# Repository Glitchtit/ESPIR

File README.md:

# ESPIR — Zigbee IR Blaster for Home Assistant

A Home Assistant–controlled IR blaster built on the **ESP32-C6**, connected over
**Zigbee** to a **Zigbee2MQTT (Z2M)** coordinator. It **learns** IR codes from your
existing physical remotes and **replays** them on command, so HA buttons map 1:1 to
"press button → appliance fires the learned signal."

## Topology

```
[remote] --IR--> [VS1838B] --RMT RX--> MASTER (DevKitC-1, USB, Zigbee Router)
                                          |  NVS slots, custom ZCL cluster 0xFC00
                                          |  +--RMT TX--> [SZHJW] --IR--> appliance
                                          v
                       Zigbee <--> Z2M (z2m/espir.js) <--> Home Assistant
                                          |                       |
                              learn / send / read code     buttons + scripts
                                          v
        replication (HA script): copy master's learned code -> each SLAVE
                                          v
                       SLAVE (XIAO C6, LiPo, Sleepy End Device) --IR--> local appliance
```

- **Master** (ESP32-C6-DevKitC-1, USB-powered Zigbee **Router**): **learns** by raw-capturing
  from a **VS1838B** receiver and **transmits** through an **SZHJW** dual-LED module — both on
  the RMT peripheral; stores codes in NVS. Always-on, so it responds instantly and extends the
  Zigbee mesh.
- **Slave** (Seeed XIAO ESP32-C6, LiPo **Sleepy End Device**): transmit-only repeater for
  coverage in another spot, using the SZHJW dual-LED emitter (RMT). Receives learned codes
  from the master via a replication path.

> **Protocol note:** raw capture learns essentially **any** remote; NEC is auto-compacted to
> `{address, command}` for cheap storage/replication. Master and slaves share the RMT backend,
> so codes are fully interoperable.

## Why this design

A battery IR blaster that must answer HA instantly is a contradiction — Zigbee on the C6
only sips power if it sleeps deeply. The master/slave split sidesteps it: the master is
mains/USB-powered (snappy, full range, does the learning); slaves are battery and only need
to fire eventually at their own nearby appliance.

## Repo layout

| Path | What |
|------|------|
| `components/espir_ir`    | RMT IR transmit (software 38 kHz carrier) + raw receive |
| `components/espir_codec` | NEC decode/encode + raw↔compact helpers |
| `components/espir_store` | NVS slot store (save/load/clear, chunked program) |
| `components/espir_zcl`   | Custom ZCL cluster `0xFC00` contract (`espir_proto.h`) |
| `components/espir_device`| Zigbee device: endpoint, cluster server, learn FSM (shared) |
| `components/espir_led`   | RGB status LED (LEDC PWM) for the custom-PCB slave |
| `components/espir_oled`  | 0.91″ SSD1306 128×32 I²C status display for the master |
| `master/`                | ESP-IDF app: VS1838B learn + SZHJW transmit (Router) |
| `slave/`                 | ESP-IDF app: SZHJW transmit + program/send (Sleepy End Device) |
| `slave-pcb/`             | Custom-PCB slave firmware: discrete MOSFET IR driver + RGB status LED (XIAO-carrier pinout) |
| `z2m/espir.js`           | Zigbee2MQTT external converter (mirrors the cluster contract) |
| `homeassistant/`         | Replication script + example button entities |
| `hardware/`              | BOM + wiring; incl. [`pcb-fully-custom.md`](hardware/pcb-fully-custom.md) — the fully-custom discrete-ESP32-C6 slave board |
| `docs/specs/`            | Design spec |

## Wiring & pinout

Pins are defaults — override in `idf.py menuconfig → ESPIR Configuration`. All grounds must
be common. Full notes (caps, boost, battery sense) in
[`hardware/wiring-master.md`](hardware/wiring-master.md) and
[`hardware/wiring-slave.md`](hardware/wiring-slave.md).

### Master — ESP32-C6-DevKitC-1 (USB powered)

The master uses an **SZHJW** dual-LED module (RMT) for **transmitting** and a **VS1838B**
38 kHz receiver (RMT raw capture) for **learning** — both straight on the C6. Raw capture
learns **any** remote protocol; NEC is auto-compacted.

| Signal | C6 GPIO | Connects to |
|--------|---------|-------------|
| IR TX data | **GPIO6** | SZHJW `DAT` |
| IR RX data | **GPIO4** | VS1838B `OUT` |
| OLED I²C SDA | **GPIO22** | SSD1306 `SDA` |
| OLED I²C SCL | **GPIO23** | SSD1306 `SCK` (= SCL) |
| 5 V | `5V` pin | SZHJW `VCC` |
| 3.3 V | `3V3` pin | VS1838B `VCC` (**3.3 V only**) **and** SSD1306 `VCC` |
| GND | any `GND` | SZHJW `GND`, VS1838B `GND` **and** SSD1306 `GND` |

An optional **0.91″ SSD1306 128×32 I²C OLED** (addr 0x3C) shows the active slot, whether it
holds a code (`STORED`/`EMPTY`), and learn/connection state. Set `ESPIR_OLED_ENABLE=n` to omit
it — the firmware runs normally without a panel.

```
DevKitC-1                         SZHJW dual-LED TX (5 V) — SEND
  5V    ──────────────────────────► VCC
  GPIO6 ──────────────────────────► DAT
  GND ──────────────┬─────────────► GND
                    │
  3V3 ──────────────┼─────────────► VCC   VS1838B receiver (3.3 V ONLY) — LEARN
  GPIO4 ◄───────────┼────────────── OUT
  GND ──────────────┴─────────────► GND
```

Power the VS1838B at **3.3 V** (its `OUT` drives a GPIO directly). Avoid GPIO12/13
(USB-Serial-JTAG) and strapping pins GPIO8/9/15. (The YS-IRTM module is no longer used.)

### Slave — Seeed XIAO ESP32-C6 (LiPo powered, transmit-only)

No 5 V rail on battery, so the transmitter runs at battery voltage (~3.7–4.2 V → reduced
range). No receiver.

| Signal | XIAO pad | C6 GPIO | Connects to |
|--------|----------|---------|-------------|
| IR TX data | **D2** | GPIO2 | SZHJW `DAT` |
| Power for IR TX | `BAT+` (or `5V` on USB) | — | SZHJW `VCC` |
| GND | `GND` | — | SZHJW `GND` |
| LiPo ± | `BAT+` / `BAT−` | — | 3.7 V LiPo cell (charges over USB-C) |

```
XIAO ESP32-C6                     SZHJW IR TX (2× 940nm emitters)
  BAT+ ──────────────────────────► VCC   (≈3.7–4.2 V; reduced range)
  D2 (GPIO2) ────────────────────► DAT
  GND ───────────────────────────► GND
  BAT+ / BAT− ◄──────────────────── 3.7 V LiPo cell
```

### Custom slave PCBs (permanent builds)

Two ways to turn the jumper-wire slave into a board:

1. **XIAO-carrier** — reflow a XIAO ESP32-C6 onto a small PCB + a discrete IR driver + RGB status
   LED. See [`hardware/wiring-slave.md` → Custom PCB](hardware/wiring-slave.md#custom-pcb-xiao-esp32-c6-as-an-smd-part).
2. **Fully custom (bare ESP32-C6)** — a complete standalone board: discrete C6 (QFN-40) with its own
   USB-C, MCP73831 LiPo charger, AP2112K LDO + load-share, chip antenna (+ u.FL), SPI flash and
   40 MHz crystal, the 2-LED IR driver, and an addressable RGB status LED. Verified to meet the
   slave requirements (Zigbee, battery+charging, USB-C flash/power). See
   [`hardware/pcb-fully-custom.md`](hardware/pcb-fully-custom.md). *(Hardware designed in EasyEDA
   Pro; it moves the IR pin to GPIO2 and the status LED to a single GPIO11 data line, so it needs a
   firmware variant — noted in that doc.)*

## Build & flash

Requires ESP-IDF v5.4+ (`. ~/esp/esp-idf/export.sh` to load the environment).
See [`AGENTS.md`](AGENTS.md) for the full command reference.

```sh
. ~/esp/esp-idf/export.sh

# Master (on the DevKitC-1)
cd master && idf.py set-target esp32c6 && idf.py build flash monitor

# Slave (on the XIAO C6)
cd slave  && idf.py set-target esp32c6 && idf.py build flash monitor

# Custom-PCB slave (XIAO C6 + discrete IR driver + RGB status LED)
cd slave-pcb && idf.py set-target esp32c6 && idf.py build flash monitor
```

## Pairing & usage

1. Drop `z2m/espir.js` into your Z2M `external_converters/` and restart Z2M.
2. Enable joining in Z2M; power on the device; it joins and appears with learn/send entities.
3. To learn: set the target slot, trigger **learn**, point the remote at the master's
   receiver, press the remote key. The captured code is stored in that slot.
4. Bind an HA button to **send slot N**. To cover another room, replicate the code to a
   slave (see `homeassistant/replicate-codes.yaml`).

The HA **Slot** selector drives the device over the `selectSlot` command (manufacturer-specific
ZCL attributes aren't OTA-writable on zboss). The device reports the active slot and whether it
holds a code back to HA (`slot_occupied`) and to the master OLED.

## Over-the-air updates

The master **and both slave builds** support Zigbee OTA firmware updates via Zigbee2MQTT.

**One-time migration:** the OTA-capable firmware uses a new dual-slot partition table,
so the first time you load it you must flash that device over USB (`cd <app> && idf.py flash`,
where `<app>` is `master`, `slave`, or `slave-pcb`). The device re-pairs to your Zigbee
network once after this flash. All later updates are wireless. (Slaves are sleepy end
devices, so their wireless transfers are slower — do them on good battery/USB power.)

**Point Z2M at the image index** — in your Zigbee2MQTT `configuration.yaml`:

    ota:
      zigbee_ota_override_index_location: https://raw.githubusercontent.com/Glitchtit/ESPIR/main/z2m/ota/index.json

Restart Z2M. Each ESPIR device then appears in the OTA tab. Click "Check", then "Update"
when a newer version is offered. The device downloads in the background, reboots into the
new firmware, and confirms it; a bad image rolls back automatically on next boot.

## Status

Firmware and host integration are written and **both apps build clean** for esp32c6
(ESP-IDF v5.4, esp-zigbee-lib 1.6.8):

- ✅ Shared components (`espir_ir` RMT TX/RX, `espir_codec` NEC+raw, `espir_store` NVS slots)
- ✅ Master app — Zigbee Router, custom cluster `0xFC00`, learn FSM
- ✅ Master OLED (`espir_oled`) — active slot, `STORED`/`EMPTY`, learn/connection state
- ✅ Slave app — Zigbee Sleepy End Device, transmit-only
- ✅ Z2M converter, HA replication script, hardware docs

**Verified on hardware:** the master pairs to Zigbee2MQTT, exposes the custom cluster,
status fields populate live in HA, learn/send work end-to-end over the RMT path, and the OLED
tracks the active slot + `STORED`/`EMPTY` occupancy live. Wire the
master per [`hardware/wiring-master.md`](hardware/wiring-master.md) (SZHJW on GPIO6, VS1838B on
GPIO4 at 3.3 V, SSD1306 on GPIO22/23). **Remaining:** flash/pair the XIAO **slave** and exercise
the replication path (`homeassistant/replicate-codes.yaml`).

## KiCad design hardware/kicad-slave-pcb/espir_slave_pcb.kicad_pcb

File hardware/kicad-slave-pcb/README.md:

# ESPIR slave PCB — KiCad

The KiCad realization of the ESPIR fully-custom slave board. The original is
captured in EasyEDA Pro (see [`../pcb-fully-custom.md`](../pcb-fully-custom.md));
that board file "lives in the EasyEDA workspace, not in git." This directory is
the same circuit rebuilt **in KiCad**, fully in-repo and reproducible from source.

Schematic (connect-by-name net labels), placement, and the autorouted board:

## What this is

The circuit is described **as code** with [SKiDL](https://github.com/devbisme/skidl)
(`espir_slave_pcb.py`) — a Python netlist HDL that looks up real KiCad library
symbols and emits an authoritative KiCad netlist. From that one netlist:
`make_schematic.py` generates an openable **`.kicad_sch`** (every part + a net
label on each pin — connect-by-name), and `kinet2pcb` + a `pcbnew` script produce
the **`.kicad_pcb`** (footprints, nets, functional placement, board outline).

```
                    ┌─ make_schematic.py ─▶  espir_slave_pcb.kicad_sch  (schematic)
espir_slave_pcb.py ─┤  (+ SKiDL ERC)
   (the circuit)    └─ espir_slave_pcb.net ─ kinet2pcb ─▶ espir_slave_pcb.kicad_pcb ─ place_and_outline.py
```

| File | What |
|------|------|
| `espir_slave_pcb.py`     | **The circuit** — SKiDL source (parts + nets). The schematic-of-record. |
| `espir_slave_pcb.net`    | Generated KiCad netlist (authoritative connectivity). |
| `make_schematic.py`      | netlist → `.kicad_sch` (real symbols embedded; connect-by-name labels). |
| `espir_slave_pcb.kicad_sch` | KiCad schematic: 38 components, 25 nets — connectivity is an **exact match** to the netlist. |
| `place_and_outline.py`   | `pcbnew` pass: 4-layer setup + functional placement + Edge.Cuts + Power/IR net classes. |
| `route.sh`               | Autoroute via Freerouting (DSN → SES). KiCad has no built-in headless autorouter. |
| `pour_gnd.py`            | GND pours on all 4 layers + solid GND-pad connection + collision-checked via stitching. `planes-only` mode pours the planes without stitching (run before routing). |
| `fix_silk.py`            | Collision-aware silkscreen designator placement; hides refs with no clear spot. |
| `en_jumper.py`           | Jumpers the LDO EN→VIN tie on B.Cu (boxed pins Freerouting can't tie). |
| `mounting_and_round.py`  | Expand X (centred), round the corners (r=3 mm), add 4× M3 mounting holes. |
| `swap_smd_button.py`     | Swap one button THT→SMD on the routed board (bridge signal, reconnect inner layers via a via, GND via pour). |
| `espir_slave_pcb.kicad_pcb` | **4-layer** KiCad board: 38 footprints, **fully routed**, 0.5 mm power incl. VBAT, GND planes, centred on A4. |
| `espir_slave_pcb.kicad_dru` | Critical-signal **routing rules** (power width, IR-pulse width, sense-vs-IR clearance, USB width) — DRC auto-enforces them. |
| `espir_slave_pcb.kicad_pro` | KiCad project (open this). |
| `build.sh`               | Reproduces everything from source. |

> The schematic uses **connect-by-name net labels** (a label on every pin) rather
> than drawn wires — the standard scriptable way to express a netlist graphically.
> KiCad re-extracts the identical 25-net netlist from it (verified). Its ERC items
> (off-grid label endpoints, floating NC pins, power-pin-not-driven, lib-symbol
> cache mismatch) are cosmetic, not connectivity errors. Drawing wires / tidy
> placement is GUI finishing work.

## Adjustment vs the EasyEDA discrete-C6 board

Per request this build uses the **ESP32-C6-MINI-1 module** instead of the bare
ESP32-C6 QFN-40. The module integrates the SPI flash, 40 MHz crystal + load caps,
RF chip antenna + π-match, and the EP grounding — so the circuit **drops** those
discrete parts entirely:

| Dropped (now internal to the module) | Was in the discrete design |
|---|---|
| `U4` W25Q32 flash + decoupling | external SPI flash |
| `X1` 40 MHz crystal + `C9`/`C10` | external crystal + load caps |
| `AE1` chip antenna, `RF1` u.FL, `R2`/`R3`/`R4` π-match | external antenna chain |

Everything else carries over: USB-C + load-share + LiPo-charger power tree,
AP2112K 3V3 LDO, 2-LED discrete IR driver, addressable RGB status LED,
battery/VBUS sense dividers, reset/boot buttons, battery slide switch.

**GPIO remap:** the MINI-1 module does not bring out GPIO11, so the WS2812
status-LED data line moves **GPIO11 → GPIO7** (a free, non-strapping exposed pin).
All other pins are unchanged: IR on GPIO2, battery/VBUS sense on GPIO4/GPIO5,
USB on GPIO12/GPIO13, boot on GPIO9, strap pull-up on GPIO8.

> The `slave-pcb/` firmware would need the same one-line pin change
> (`WS_GPIO 11 → 7`) it already needs for this board family.

## Bill of materials (38 parts)

ESP32-C6-MINI-1 module · AP2112K-3.3 LDO · MCP73831 LiPo charger · AO3401A
load-share P-FET · B5819W (1N5819) OR-ing Schottky · AO3400A IR-driver N-FET ·
2× IR333C 940 nm IR LED · WS2812 RGB status LED · charge LED · USB-C (HRO
TYPE-C-31-M-12) · JST-SH LiPo connector · SS12D07VG6 slide switch · 2× SMD tactile (KMR2)
buttons · 17 resistors · 7 capacitors. Full values + LCSC numbers are in
[`../pcb-fully-custom.md`](../pcb-fully-custom.md).

## Build / reproduce

```bash
sudo pacman -S --needed kicad kicad-library kicad-library-3d  # -3d = component 3D models
python -m venv --system-site-packages .venv && . .venv/bin/activate
pip install skidl kinet2pcb
./build.sh
```

> Without `kicad-library-3d` the 3D viewer shows only bare pads on green FR4. The
> ESP32-C6-MINI-1 module has no stock 3D model (renders as pads even with it installed);
> add the vendor STEP and point U5's footprint `(model …)` at it if you want its body.

## Verification

- **ERC (SKiDL): 0 errors.** The 18 warnings are all *intentional* unconnected
  pins — the module's spare GPIOs (IO0/1/3/6/14/15/18–23, RXD0/TXD0), the USB-C
  SBU pins, the slide-switch OFF throw, and the WS2812 DOUT (no daisy-chain).
  Every wired pin lands on the right net.
- **Schematic (`kicad-cli sch export netlist`):** KiCad loads the generated
  `.kicad_sch` and re-extracts the **exact same 25 multi-pin nets** as the SKiDL
  netlist (verified set-equal). The schematic is a faithful graphical view of the
  circuit.
- **4-layer stackup** (F / In1 / In2 / B) with **GND pours on all four layers** + a
  collision-checked stitching-via grid — the inner copper acts as ground reference planes
  for stability. The extra routing room lets **every power rail, incl. VBAT, route at 0.5 mm**.
- **Pour order: GND planes are poured *before* routing** (`pour_gnd.py planes-only`), so the
  Specctra DSN exports GND as `(plane …)` per layer and Freerouting routes **only the signal
  nets** — no redundant GND traces, just the pad-to-plane vias GND needs. A full `pour_gnd.py`
  after routing re-fills around the new tracks and adds stitching.
- **Routing (`route.sh` → Freerouting, 4-layer):** **fully routed — 114/114** (310 tracks,
  43 vias incl. stitching). All `Power`-class rails are 0.5 mm. The LDO EN pin (tied to VSYS,
  boxed between U6's VIN/GND pins) is jumpered VIN→EN on B.Cu under the GND pin.
- **Module placement:** U5's body is at the **top edge so the antenna `tracks not_allowed`
  keep-out hangs OFF the board** — otherwise it covers the interior and the parts under it
  can't route.
- **Board centred** on the A4 drawing sheet (148.5, 105 mm).
- **Mechanical: 66 × 47 mm, rounded corners (r=3 mm), 4× M3 mounting holes** in the
  expanded left/right margins (clear of all components; GND pour isolates them).
- **DRC (`kicad-cli pcb drc`): 0 electrical violations** — 0 unconnected, 0 track-width,
  0 clearance, 0 copper-edge, 0 shorts. Remaining: **4 `silk_edge_clearance`** (U5 antenna +
  USB-C outlines overhanging their edges, by design — fab clips edge silk) and **1
  `lib_footprint_mismatch`** (U5 board copy vs the latest library version — same 61 pads,
  benign). LED2/USBC1 silk refs hidden (saturated cluster; still in BOM/CPL).

## Remaining work (the human finishing pass)

Same division of labour the EasyEDA workflow uses — the circuit + a clean,
function-grouped starting layout are done; the fab finishing is left to a human:

1. **Edge clearance for passives:** `place_and_outline.py` now enforces ≥1 mm board-edge
   clearance for every non-port/antenna part and places the USB-C CC pulldowns right at the
   connector. In the **committed board** the charge LED (LED2) + its ballast (R14) still sit
   ~0.8 mm from the bottom edge (within fab spec, but tight). Pushing them further means
   re-placing the dense USB-C/charger/divider cluster — a fresh `build.sh` regen applies the
   improved placement, but the bottom-center density leaves the **LDO EN tie + IR gate stub**
   for a short KiCad GUI routing session (interactive routing handles them trivially). The
   committed `.kicad_pcb` stays the verified-clean artifact.
2. **Optional polish:** trim U5/USB-C footprint silk that overhangs the edges (the 4 benign
   `silk_edge_clearance`), or leave it (fab clips it). For a true 90 Ω USB pair, rename
   `USB_DM`/`USB_DP` → `USB_D-`/`USB_D+`, set the stackup, Route → Differential Pair + Tune Skew.
2. ~~GND copper pours~~ — done (`pour_gnd.py`: all 4 layers + stitching vias).
3. Nudge silkscreen, confirm the **antenna keep-out** is clear of copper and the
   module antenna overhangs the top edge, verify **edge connectors** (USB-C bottom,
   JST left, buttons right) sit flush at their edges.
4. Set net-class track widths (Power/IR already declared in the project) and
   export Gerber/BOM/CPL.

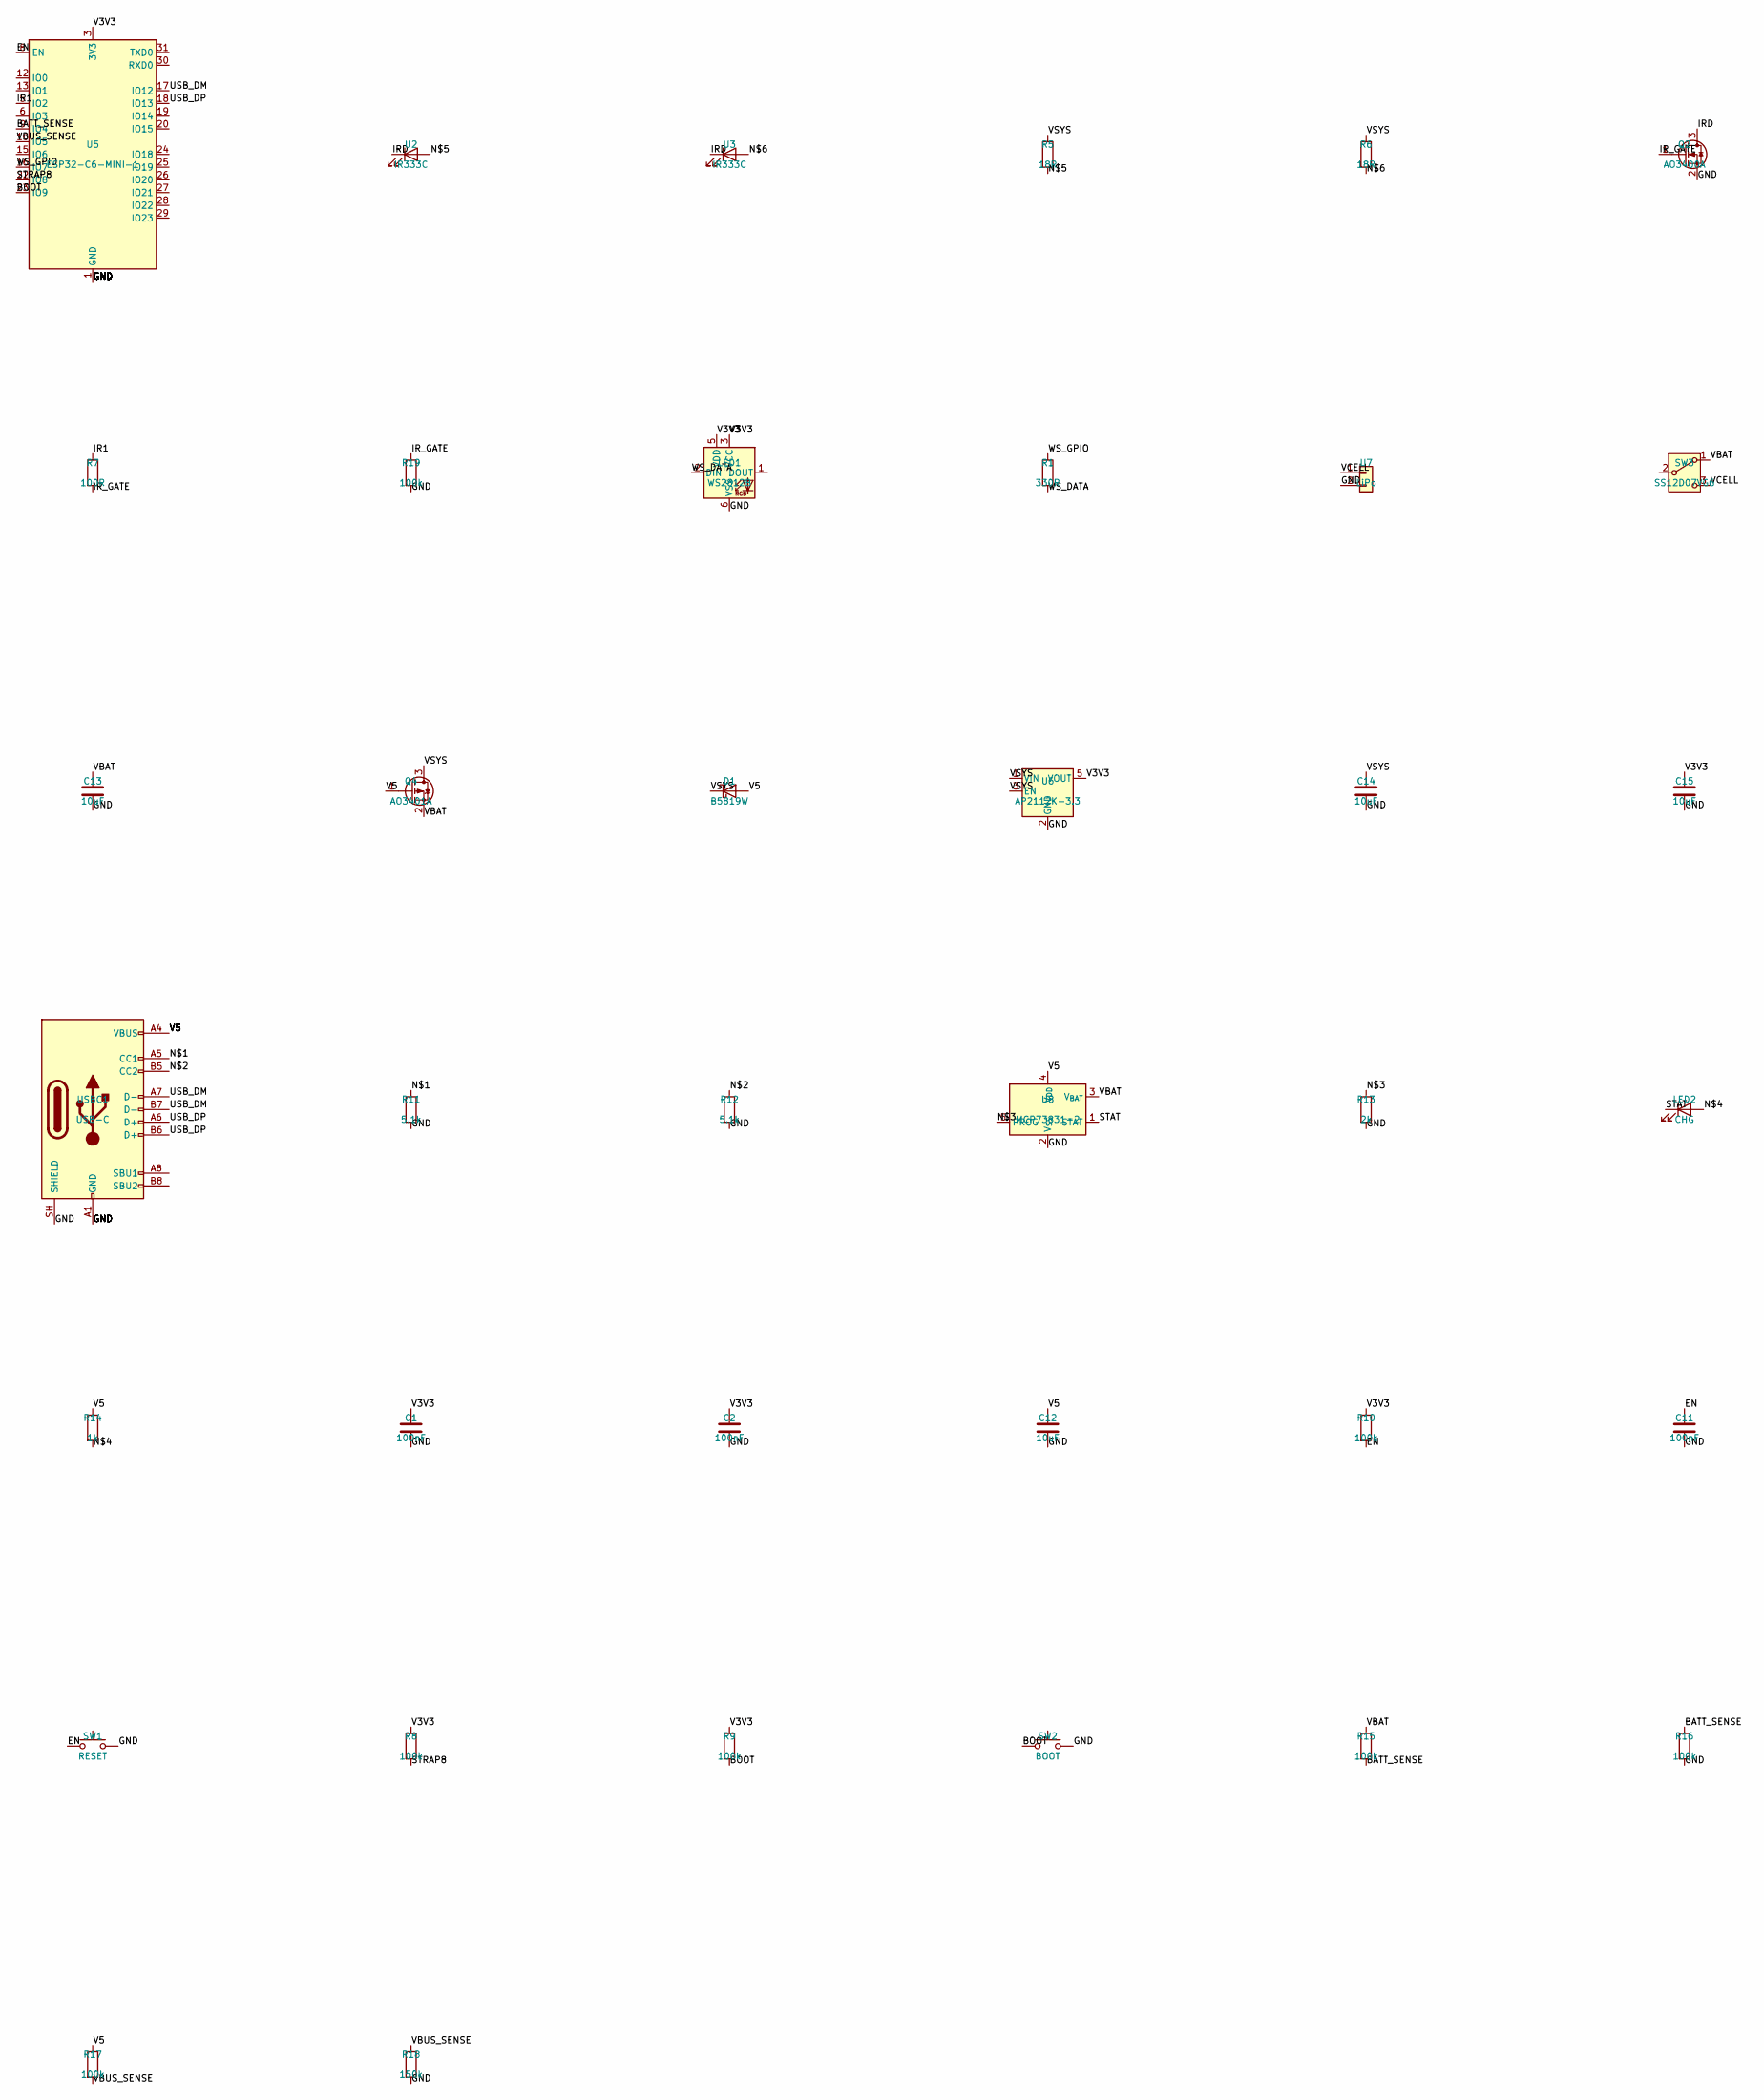
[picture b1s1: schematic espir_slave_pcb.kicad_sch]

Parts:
C1, C2, C11: 100nF; C_0603_1608Metric
C12, C13, C14, C15: 10uF; C_0805_2012Metric
D1: B5819W; D_SOD-123
LED1: WS2812B; LED_WS2812_PLCC6_5.0x5.0mm_P1.6mm
LED2: CHG; LED_0603_1608Metric
Q2: AO3400A; SOT-23
Q4: AO3401A; SOT-23
R1: 330R; R_0603_1608Metric
R5, R6: 18R; R_0603_1608Metric
R7: 100R; R_0603_1608Metric
R8, R9, R10, R15, R16, R17, R19: 100k; R_0603_1608Metric
R11, R12: 5.1k; R_0603_1608Metric
R13: 2k; R_0603_1608Metric
R14: 1k; R_0603_1608Metric
R18: 150k; R_0603_1608Metric
SW1: RESET; SW_PUSH_6mm
SW2: BOOT; SW_PUSH_6mm
SW3: SS12D07VG6; SW_SPDT_Shouhan_MSK12C02
U2, U3: IR333C; LED_D5.0mm
U5: ESP32-C6-MINI-1
U6: AP2112K-3.3; SOT-23-5
U7: LiPo; JST_SH_SM02B-SRSS-TB_1x02-1MP_P1.00mm_Horizontal
U8: MCP73831-2; SOT-23-5
USBC1: USB-C; USB_C_Receptacle_HRO_TYPE-C-31-M-12

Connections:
BATT_SENSE: R15.2, R16.1, U5.9 (IO4)
BOOT: R9.2, SW2.1, U5.23 (IO9)
EN: C11.1, R10.2, SW1.1, U5.8 (EN)
GND: C1.2, C2.2, C11.2, C12.2, C13.2, C14.2, C15.2, LED1.6 (VSS), Q2.2 (S), R11.2, R12.2, R13.2, R16.2, R18.2, R19.2, SW1.2, SW2.2, U5.1 (GND), U5.2 (GND), U5.11 (GND), U5.14 (GND), U5.36 (GND), U5.37 (GND), U5.38 (GND), U5.39 (GND), U5.40 (GND), U5.41 (GND), U5.42 (GND), U5.43 (GND), U5.44 (GND), U5.45 (GND), U5.46 (GND), U5.47 (GND), U5.48 (GND), U5.49 (GND), U5.50 (GND), U5.51 (GND), U5.52 (GND), U5.53 (GND), U6.2 (GND), U7.2, U8.2 (V_{SS}), USBC1.A1 (GND), USBC1.A12 (GND), USBC1.B1 (GND), USBC1.B12 (GND), USBC1.SH (SHIELD)
IR1: R7.1, U5.5 (IO2)
IRD: Q2.3 (D), U2.1 (K), U3.1 (K)
IR_GATE: Q2.1 (G), R7.2, R19.1
unnamed: R11.1, USBC1.A5 (CC1)
unnamed: R12.1, USBC1.B5 (CC2)
unnamed: R13.1, U8.5 (PROG)
unnamed: LED2.2 (A), R14.2
unnamed: R5.2, U2.2 (A)
unnamed: R6.2, U3.2 (A)
STAT: LED2.1 (K), U8.1 (STAT)
STRAP8: R8.2, U5.22 (IO8)
USB_DM: U5.17 (IO12), USBC1.A7 (D-), USBC1.B7 (D-)
USB_DP: U5.18 (IO13), USBC1.A6 (D+), USBC1.B6 (D+)
V3V3: C1.1, C2.1, C15.1, LED1.3 (VCC), LED1.5 (VDD), R8.1, R9.1, R10.1, U5.3 (3V3), U6.5 (VOUT)
V5: C12.1, D1.2 (A), Q4.1 (G), R14.1, R17.1, U8.4 (V_{DD}), USBC1.A4 (VBUS), USBC1.A9 (VBUS), USBC1.B4 (VBUS), USBC1.B9 (VBUS)
VBAT: C13.1, Q4.2 (S), R15.1, SW3.1 (A), U8.3 (V_{BAT})
VBUS_SENSE: R17.2, R18.1, U5.10 (IO5)
VCELL: SW3.3 (C), U7.1
VSYS: C14.1, D1.1 (K), Q4.3 (D), R5.1, R6.1, U6.1 (VIN), U6.3 (EN)
WS_DATA: LED1.2 (DIN), R1.2
WS_GPIO: R1.1, U5.16 (IO7)

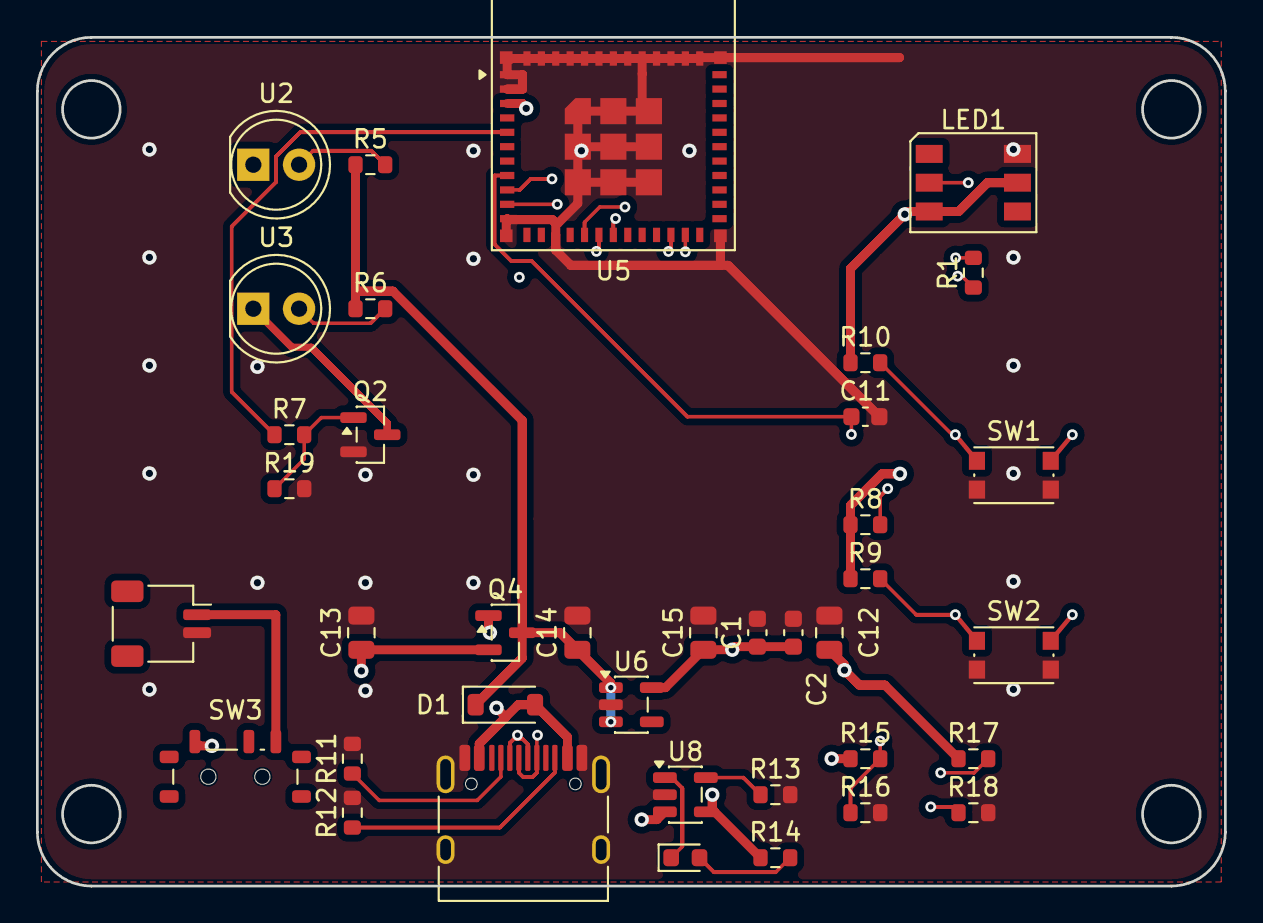
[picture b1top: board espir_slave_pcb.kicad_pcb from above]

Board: 4 copper layers, 66.0 x 47.1 mm, 38 parts (0 on the bottom side), 25 nets.

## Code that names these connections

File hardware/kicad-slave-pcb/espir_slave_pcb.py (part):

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VCELL = Net('VCELL')       # raw cell terminal (upstream of the slide switch)
V3V3  = Net('V3V3')        # AP2112K output, powers the module

IR_GATE = Net('IR_GATE')   # GPIO2 -> series R -> Q2 gate
IRD     = Net('IRD')       # IR-LED cathodes <-> Q2 drain (pulsed LED current)
WS_DATA = Net('WS_DATA')   # GPIO7 -> series R -> WS2812 DIN  (was GPIO11)
USB_DP  = Net('USB_DP')    # GPIO13
USB_DM  = Net('USB_DM')    # GPIO12
BATT_SENSE = Net('BATT_SENSE')  # GPIO4 (ADC1)
VBUS_SENSE = Net('VBUS_SENSE')  # GPIO5 (ADC1)
EN      = Net('EN')        # module reset
BOOT    = Net('BOOT')      # GPIO9 download-mode button
STAT    = Net('STAT')      # MCP73831 open-drain charge status
IR1     = Net('IR1')       # GPIO2 raw drive (pre series-R)
WS_GPIO = Net('WS_GPIO')   # GPIO7 raw drive (pre series-R)
STRAP8  = Net('STRAP8')    # GPIO8 strap pull-up node

# Mark the source rails as driven so ERC doesn't flag power-input-not-driven.
# (V3V3 is driven by the LDO VOUT and VBAT by the charger, so they don't need it.)
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U5['GND'] += GND          # all GND pins (incl. module EP) -> GND
U5['EN']  += EN
U5['IO2'] += IR1          # GPIO2 IR drive (pre series-R)
U5['IO7'] += WS_GPIO      # GPIO7 status-LED drive (pre series-R)
U5['IO4'] += BATT_SENSE
U5['IO5'] += VBUS_SENSE
U5['IO12'] += USB_DM      # USB D-
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# ----------------------------------------------------------------------------
U8 = Part('Battery_Management', 'MCP73831-2-OT', value='MCP73831-2',
          footprint=SOT235, ref='U8')
# Pin names carry LaTeX braces (V_{DD}); address by number: 1 STAT,2 VSS,3 VBAT,4 VDD,5 PROG
U8[4] += V5      # VDD
U8[2] += GND     # VSS
U8[3] += VBAT    # VBAT
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SW2 = Part('Switch', 'SW_Push', value='BOOT',
           footprint='Button_Switch_SMD:SW_Push_1P1T_NO_CK_KMR2', ref='SW2')
SW2[1] += BOOT; SW2[2] += GND
R8 = Part('Device', 'R', value='100k', footprint=R0603, ref='R8'); V3V3 += R8[1]; R8[2] += STRAP8   # GPIO8 strap pull-up
R9 = Part('Device', 'R', value='100k', footprint=R0603, ref='R9'); V3V3 += R9[1]; R9[2] += BOOT     # GPIO9 strap pull-up

# ----------------------------------------------------------------------------
# IR sender — GPIO2 -> R7 -> Q2 gate (with pulldown); 2 IR LEDs on VSYS via R5/R6
# ----------------------------------------------------------------------------
R7  = Part('Device', 'R', value='100R', footprint=R0603, ref='R7')  # gate series
IR1 += R7[1]; R7[2] += IR_GATE
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# Addressable RGB status LED — GPIO7 -> R1 -> WS2812 DIN  (powered from 3V3)
# ----------------------------------------------------------------------------
R1 = Part('Device', 'R', value='330R', footprint=R0603, ref='R1')
WS_GPIO += R1[1]; R1[2] += WS_DATA
LED1 = Part('LED', 'WS2812', value='WS2812B',
            footprint='LED_SMD:LED_WS2812_PLCC6_5.0x5.0mm_P1.6mm', ref='LED1')
LED1['VDD'] += V3V3
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
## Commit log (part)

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2026-06-23 Scaffold ESPIR: docs, hardware refs, Z2M converter, HA glue, protocol contract
2026-06-23 Add shared firmware components (IR/codec/store) + bench build verified
2026-06-23 Add slave app (sleepy end device, transmit-only); builds clean
2026-06-23 README: add wiring & pinout section for master and slave
2026-06-23 Master console on UART0 (CH343 bridge port); document native-USB download trap
    Verified on hardware: master boots, YS-IRTM inits on uart1, Zigbee stack starts and
    attempts network steering. Native USB-Serial-JTAG port resets into download on port-open,
    so logs go to the CH343 UART bridge port instead (console = UART0).
2026-06-23 z2m: route custom-cluster commands to endpoint 10 (where cluster 0xFC00 lives)
2026-06-23 z2m: slot-selector + action buttons UI; read attrs on configure (no more Null)
    - Replace the learn/send/clear sliders with a 'slot' selector + an 'action' enum
    (Learn/Send/Clear) that issues the command on the selected slot.
    - Add configure() that reads the custom-cluster attributes on join/reconfigure so
    learn_status/last_*/slot_count show real values instead of Null.
    - Keep direct send_slot/learn_slot/clear_slot tz handlers for automations.
    - Drop deferred m.battery() from slave for now.
2026-06-23 Master: transmit via SZHJW (RMT) for stronger output; YS-IRTM = learn only
    The YS-IRTM's single emitter is weak. Add an SZHJW dual-LED transmitter on the RMT
    peripheral (default GPIO6, 5V) and route master sends through it; the YS-IRTM is kept for
    learning (its receiver). Only one transmitter fires per send (avoids a double-press).
    - espir_device: master do_send uses espir_ir_send (RMT) when cfg.master_rmt_tx
    - master app: espir_ir_init + new Kconfig ESPIR_MASTER_USE_SZHJW (default y) / ESPIR_TX_GPIO (6)
    - docs: wiring-master, bom, README, spec updated
2026-06-23 IR learn: capture loop keeps the longest header-led frame (fixes Samsung)
    A held/mashed remote made the RMT RX arm mid-frame and capture a short, header-less
    fragment (e.g. Samsung BN59-01303A); the inter-frame gap then ended reception. Now
    espir_ir_receive re-arms within the learn window, keeps the longest capture, and stops once
    it has a header-led frame (first mark >= 2 ms, >= 20 edges) — so a re-arm during the gap
    catches the next complete frame.
    Verified: Samsung now captures the full 67-edge frame (4546us header) and learns; AC and
2026-06-23 Slave: handle CAN_SLEEP signal (sleepy end device) + TX on D10/GPIO18
    - esp_zb_app_signal_handler: on ESP_ZB_COMMON_SIGNAL_CAN_SLEEP call esp_zb_sleep_now()
    (guarded to the end-device lib variant); was logging the signal thousands of times and
    never actually sleeping.
    - slave IR TX GPIO default 18 (XIAO D10).
    Verified: slave boots, IR init tx=18, no CAN_SLEEP flood; master still links.
2026-06-23 Slave joins: XIAO C6 antenna RF-switch init + run non-sleepy for now
    Root cause the slave never joined: the XIAO ESP32-C6 RF switch was never enabled, so the
    radio couldn't reach the network (coordinator saw zero join attempts). Configure it in the
    slave app: GPIO3=LOW enables the switch, GPIO14 selects antenna (LOW=onboard, HIGH=external
    via CONFIG_ESPIR_XIAO_EXT_ANTENNA).
    Also gate sleep behind CONFIG_PM_ENABLE and disable PM for now (sleeping during commissioning
    also blocks joining) so the slave runs as a non-sleepy ED until join+transmit are verified;
2026-06-23 Device-to-device replication: master pushes codes to slaves (long raw works)
    Replaces the HA-shuttle replication (which was capped to one Zigbee frame, so long raw codes
    like Samsung TV couldn't replicate) with direct master->slave copy over Zigbee:
    - proto: add copy_to(slot, ieee) and copy_all(ieee) commands (0x07/0x08).
    - master (espir_device.c): on copy_to/copy_all, load the slot(s) from NVS and send them to the
    target slave's endpoint 10 as program_begin/chunk/commit (chunked, ATTR_TYPE_SET raw bytes,
    64-bit addressing). Reuses the slave's existing program handler, so any length carries.
2026-06-23 Slave battery indicator (Power Config cluster) + sleep boot grace window
    - espir_device: read the LiPo via ADC1 (BAT+ ÷2 divider on GPIO0/A0), map 3.30-4.20V to 0-100%,
    and report batteryVoltage + batteryPercentageRemaining over the standard Power Config cluster
    (0x0001) every 10 min. Cluster + sampling only enabled when cfg.battery (slave).
    - cfg gains battery + battery_adc_gpio; slave main enables it (CONFIG_ESPIR_BATTERY_ADC_GPIO=0).
    - converter: slave exposes battery + battery_voltage (fz.battery parses the self-reported cluster).
    - sleep: only sleep after a 12s boot grace window — light sleep drops the native USB-JTAG, so
2026-06-23 docs: clarify D0 = A0 = GPIO0 on XIAO C6 in slave battery wiring
2026-06-23 docs: recommend 55k:55k battery divider; 1M underreads on GPIO0 even with cap
    Measured on hardware: BAT+ 4.0V gave only 1.68V at D0 with a 1M:1M+100nF divider (should be
    2.0V) — the ADC pin's DC leakage loads a divider that high-impedance, and the cap only fixes AC
    settling. Use low-impedance resistors (55k:55k, ~27k Thevenin). DIV_X100 stays 200 (still ÷2).
2026-06-23 Battery: enable automatic light sleep on slave SED (esp_pm_configure)
    The sleepy end device never powered down between polls: CONFIG_PM_ENABLE +
    tickless idle are necessary but not sufficient — esp_pm_configure() with
    light_sleep_enable must be called (and DFS auto-init is off). Without it the
    C6 idled at full clock, draining the LiPo ~2.9%/h (~1.5 day runtime) instead
    of sleeping. Mirrors the esp-zigbee / OpenThread sleepy-end-device examples.
    Guarded by CONFIG_PM_ENABLE so the mains-powered master is unaffected.
2026-06-24 slave-pcb: custom-PCB firmware with discrete IR driver + RGB status LED
    New `slave-pcb/` app target (mirrors `slave/`) for a purpose-built carrier PCB
    that reflows the XIAO ESP32-C6 as an SMD part, replaces the SZHJW module with a
    discrete low-side N-MOSFET IR driver on the same GPIO18, and adds a discrete RGB
    status LED:
    amber slow blink = searching for the network
    green solid = joined/connected (gated on USB power)
2026-06-24 hardware: note 940nm emitter rating + IR drive-current headroom
    Name the chosen 940 nm IR emitter and its ratings (Vf 1.4-2.0 V @ 350 mA,
    If 350 mA) on LED1/LED2, and add a build note: 18 Ohm (~150 mA) is a
    conservative, battery-friendly choice well under the 350 mA rating, with a
    table for dropping the ballast (~10 Ohm/250 mA, ~8.2 Ohm/300 mA) plus the
    1/2 W resistor and larger C_res caveats if more range is needed.
2026-06-24 hardware: add 100nF decoupling C14663 + on/off slide switch C2939728
    Add C3 decoupling cap (Yageo CC0603KRX7R9BB104, 100nF 50V X7R 0603, JLC
    Basic, C14663) at the XIAO power pin, alongside the C1/C2 bulk caps.
    Add SW1 battery on/off (SHOU HAN SS12D07VG6 SPDT SMD slide, C2939728) in
    series in the BAT+ line, between J1 and the XIAO BAT+ pad: OFF disconnects
    the cell (zero storage drain). It's a battery disconnect, not a hard kill —
    USB still powers the XIAO when plugged, and charging needs SW1 ON. ~300mA
2026-06-24 hardware: unify slave refdes with schematic scheme across BOM, diagrams, netlist
2026-06-25 device: add espir_info_t snapshot callback for status displays
2026-06-25 master: drive the status OLED from device info callback (Kconfig-gated)
2026-06-25 hardware: document the master SSD1306 OLED (I2C, GPIO22/23, 3.3 V)
2026-06-25 oled: unwind I2C bus on init failure; guard fb_text against negative x
2026-06-25 docs: document master OLED + slot-occupancy feedback (README, HA examples)
2026-06-28 master: dual-slot OTA partition table + app rollback
2026-06-28 espir_ota: OTA Upgrade client cluster + block writer + rollback confirm
2026-06-28 tools: make_ota.py — wrap app bin into Zigbee .ota + Z2M index
2026-06-28 z2m: declare OTA support on ESPIR-MASTER + parity guard
2026-06-28 docs: document master OTA release + update flow
2026-06-28 z2m: use ota:true for OTA support (m.ota() modernExtend absent in herdsman 26.63.0)
2026-06-28 ota: add OTA to slave + slave-pcb (per-app image type 0x0002/0x0003)
2026-06-28 docs: OTA release covers slave + slave-pcb (per-app image types)
2026-06-28 chore: gitignore AGENTS.md, homeassistant/, docs/ (untrack local-only files)
2026-06-30 hardware: autoroute the KiCad slave PCB (Freerouting)
    Add net classes (Power 0.5mm, IR 0.4mm) in place_and_outline.py so the
    current-carrying rails route wide, then autoroute headless via Freerouting
    (route.sh: pcbnew ExportSpecctraDSN -> freerouting -> ImportSpecctraSES).
    ~90% routed (310 tracks, 26 vias): 104 of 114 connections. Carrying the net
    classes into the DSN cut track_width DRC violations from 199 (uniform width)
    to 8. The last 10 (IR-LED corner + WS2812 group) are too cramped to reach on
2026-06-30 hardware: DRC fixes — fully routed, wide power, clean except benign edge silk
    Take DRC from 27 violations + 2 unrouted to 4 (all benign):
    - Re-route to 0 unrouted (114/114; 540 tracks, 27 vias).
    - Grow the right edge 1.5mm so SW1/SW2 pads + tracks clear it (8 copper_edge
    clearance -> 0).
    - Main power rails widened to 0.5mm (track_width -> 0); VBAT kept at default in
    the congested charger corner (2-layer can't widen it there without clearance
2026-06-30 hardware: enforce edge clearance for passives in the placement pipeline
    Address components sitting too close to the board edge:
    - place_and_outline.py: enforce >=1mm board-edge clearance for every
    non-port/antenna part (push inward if a courtyard is too close); move the
    USB-C CC pulldowns (R11/R12) right above the connector's CC pads so the CC
    nets route trivially; move D1 off the USB-C CC pads; charger cluster off the
    bottom edge.
2026-06-30 hardware: round corners + 4x M3 mounting holes (expand board on X)
    mounting_and_round.py (runs on the routed board — no re-route needed):
    - expand the board on X to 66mm (symmetric, stays centred) so the packed
    components get clear left/right margins;
    - round all four corners (r=3mm);
    - add 4x M3 mounting holes (3.2mm Edge.Cuts cutouts) in the new margins, clear
    of every component — the GND pour isolates them with a ring.
